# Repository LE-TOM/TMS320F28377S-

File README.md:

# TMS320F28377S-
使用176管脚的TMS320F28377S为主控引出来12路PWM和所有的模拟输入端口

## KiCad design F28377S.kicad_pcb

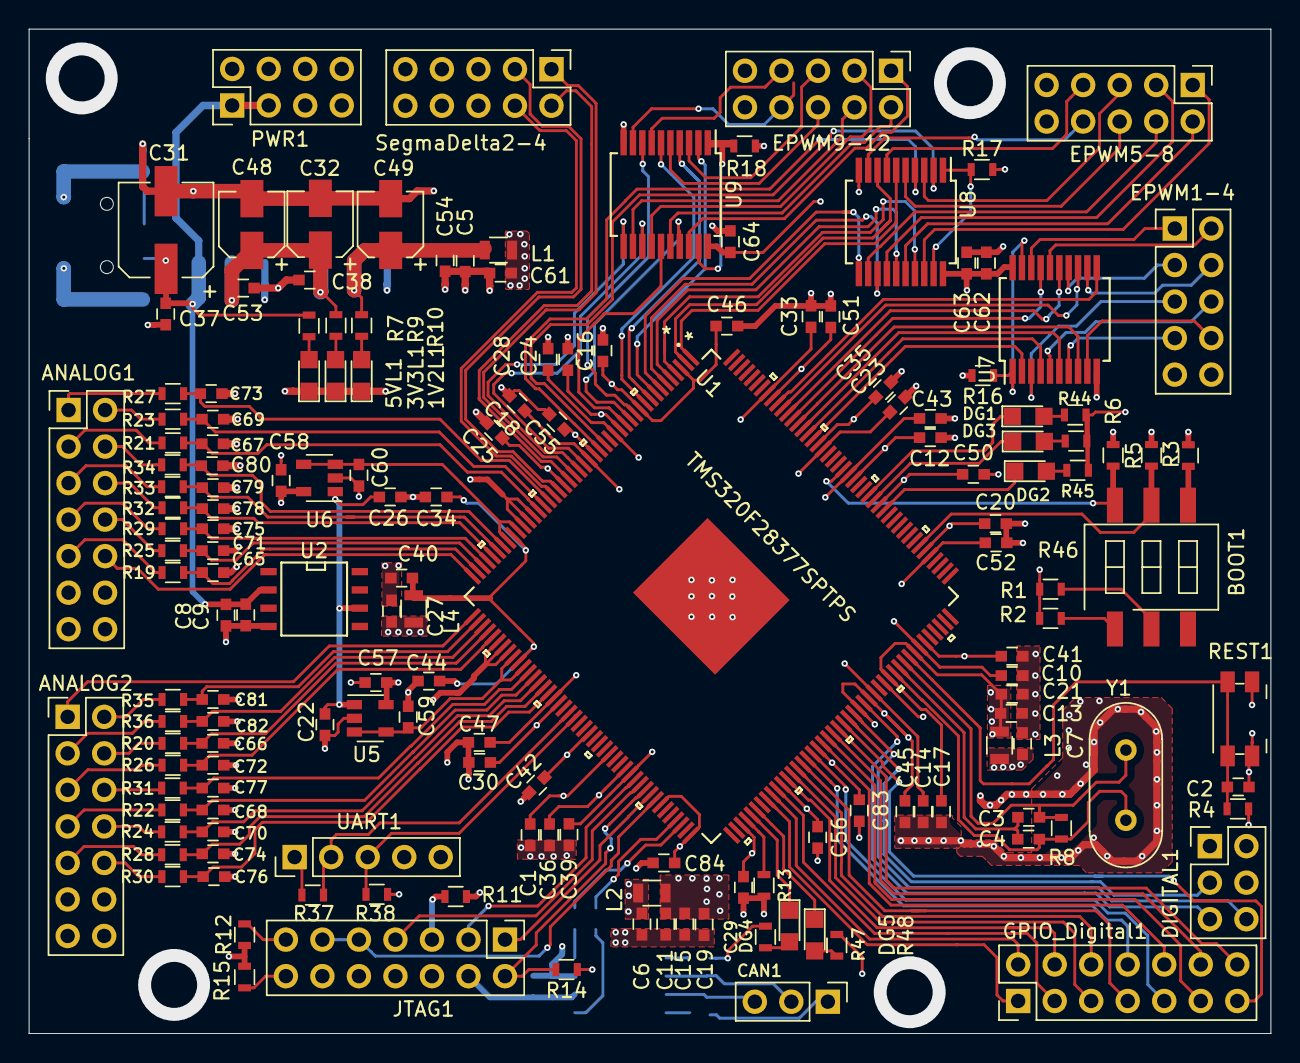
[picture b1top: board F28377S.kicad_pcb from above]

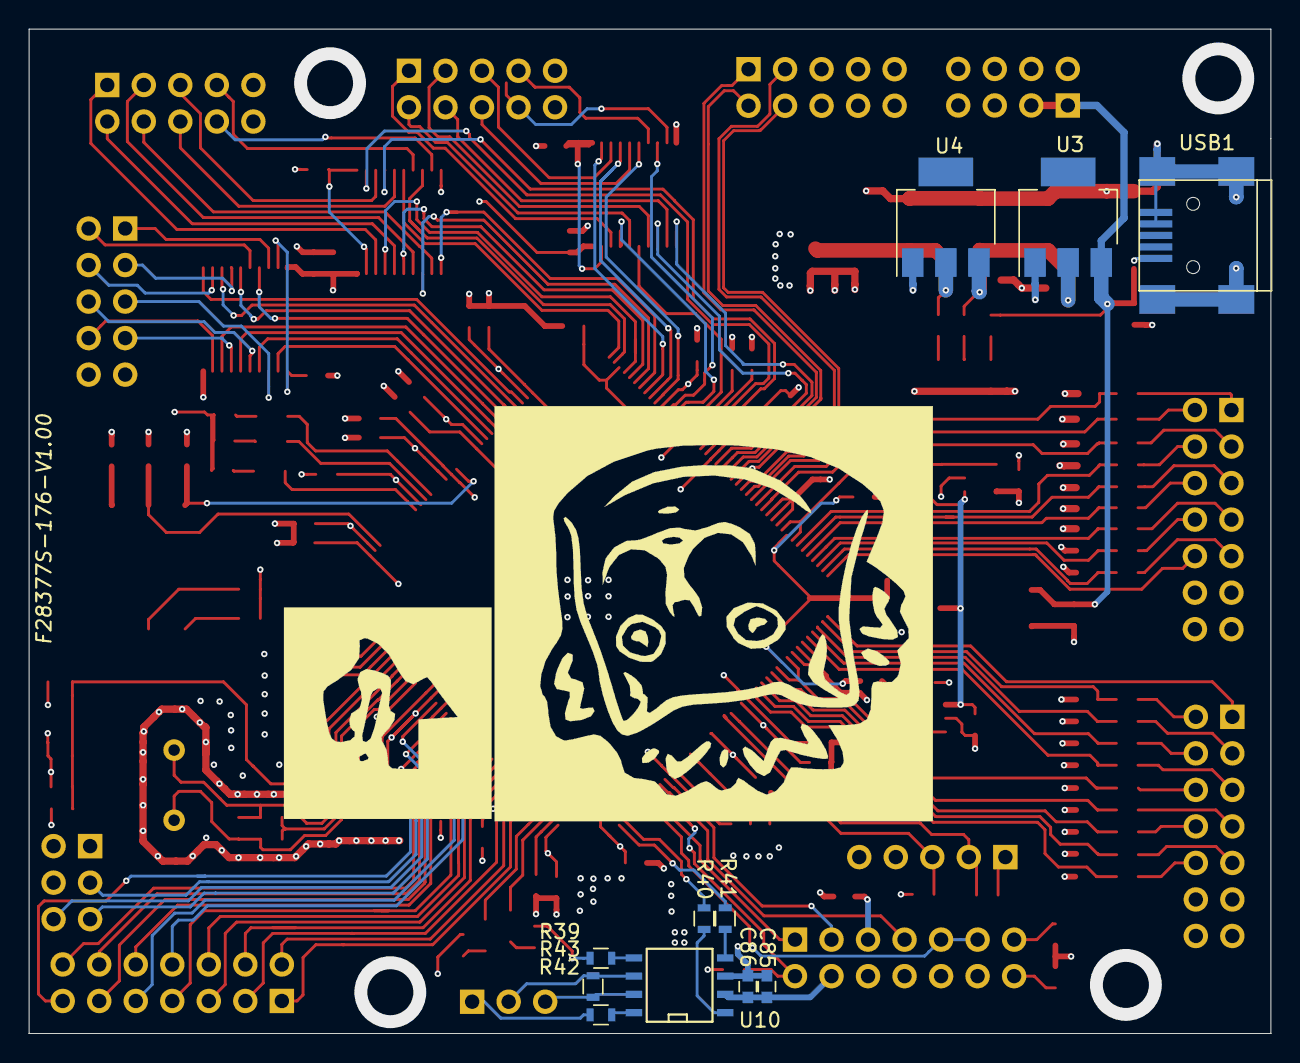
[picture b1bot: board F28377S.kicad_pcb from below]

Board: 4 copper layers, 86.4 x 69.8 mm, 172 parts (11 on the bottom side), 162 nets.

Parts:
1V2L1: BLED; LED_0805
3V3L1: GLED; LED_0805
5VL1: RLED; LED_0805
ANALOG1, ANALOG2: ANALOG; Pin_Header_Straight_2x07_Pitch2.54mm
BOOT1: BOOT; SW_DIP_x3_W8.61mm_Slide_LowProfile
C1, C2, C9, C11, C12, C15, C16, C17, C19, C20, C21, C24, C25, C26, C29, C30, C35, C36, C37, C38, C40, C41, C42, C44, C45, C46, C50, C51, C53, C54, C55, C56, C57, C58, C59, C60, C62, C63, C64, C83, C84, C86: 0.1u; C_0603
C3, C4: 25p; C_0603
C5, C6, C7, C10, C13, C14, C18, C23, C27, C28, C33, C34, C39, C43, C47, C52, C61: 2u2; C_0603
C8, C22, C85: 2.2u; C_0603
C31: 220u; CP_Elec_6.3x4.5
C32, C48, C49: 220u; CP_Elec_4x4.5
C65, C66, C67, C68, C69, C70, C71, C72, C73, C74, C75, C76, C77, C78, C79, C80, C81, C82: 100p; C_0603
CAN1: CAN; Pin_Header_Straight_1x03_Pitch2.54mm
DG1, DG2, DG3, DG4, DG5: DG1; LED_0805
DIGITAL1: DIGITAL; Pin_Header_Straight_2x03_Pitch2.54mm
EPWM1-4: EPWM1-4; Pin_Header_Straight_2x05_Pitch2.54mm
EPWM5-8: EPWM5-8; Pin_Header_Straight_2x05_Pitch2.54mm
EPWM9-12: EPWM9-12; Pin_Header_Straight_2x05_Pitch2.54mm
GPIO_Digital1: GPIO_Digital; Pin_Header_Straight_2x07_Pitch2.54mm
JTAG1: PROGRAME; Pin_Header_Straight_2x07_Pitch2.54mm
L1, L2, L3, L4: 200Ohm; R_0805
PWR1: PWR; Pin_Header_Straight_2x04_Pitch2.54mm
R1, R2: 820; R_0603
R3, R5, R6, R14: 2k2; R_0603
R4, R12, R15, R16, R17, R18, R37, R38, R39, R42: 4k7; R_0603
R7, R9, R44, R45, R46, R47, R48: 1k; R_0603
R8: 1M; R_0603
R10: 300; R_0603
R11, R19, R20, R21, R22, R23, R24, R25, R26, R27, R28, R29, R30, R31, R32, R33, R34, R35, R36, R40, R41: 100; R_0603
R13: 10k; R_0603
R43: 120; R_0603
REST1: SW_Push; Panasonic_EVQPUK_EVQPUB
SegmaDelta2-4: SegmaDelta2-4; Pin_Header_Straight_2x05_Pitch2.54mm
U1: TMS320F28377SPTPS
U2: REF196; SOIC-8-N
U3: AZ1117-3.3; SOT-223
U4: AZ1117-1.2; SOT-223
U5, U6: LM321; SOT-23-5
U7, U8, U9: 74HC244; SSOP-20_5.3x7.2mm_Pitch0.65mm
U10: SN65HVD230; SOIC-8-N
UART1: UART; Pin_Header_Straight_1x05_Pitch2.54mm
USB1: USB_B_Mini; USB_Mini-B
Y1: 10Mhz; Crystal_HC49-4H_Vertical

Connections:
+1V2: C5.1, C49.1, C54.1, L1.1, R10.1, U4.2
+3V3: ANALOG1.11, ANALOG1.12, ANALOG2.11, ANALOG2.12, C1.1, C6.1, C7.1, C27.1, C32.1, C38.1, C48.1, C53.1, C57.2, C58.2, C62.2, C63.2, C64.2, C85.2, C86.2, EPWM1-4.10, EPWM5-8.10, EPWM9-12.10, L2.1, L3.1, L4.1, PWR1.6, PWR1.8, R1.1, R2.1, R4.1, R9.1, R11.1, R12.1, R15.1, R37.1, R38.1, R39.1, R44.1, R45.1, R46.1, R47.1, R48.1, SegmaDelta2-4.6, SegmaDelta2-4.8, SegmaDelta2-4.10, U1.72, U1.119, U3.2, U4.3, U5.5, U6.5, U7.20, U8.20, U9.20, U10.3, UART1.1
+5V: C8.1, C9.1, C31.1, C37.1, PWR1.1, PWR1.3, R7.1, U2.2, U3.3, USB1.1
/ADCIN14: ANALOG1.10, U1.44
/ADCIN15: ANALOG2.1, U1.45
/ADCINA0: C65.1, R19.2, U1.43
/ADCINA1: C71.1, R25.2, U1.42
/ADCINA2: C75.1, R29.2, U1.41
/ADCINA3: C78.1, R32.2, U1.40
/ADCINA4: C79.1, R33.2, U1.39
/ADCINA5: C80.1, R34.2, U1.38
/ADCINB0: C81.1, R35.2, U1.46
/ADCINB1: C82.1, R36.2, U1.47
/ADCINB2: C66.1, R20.2, U1.48
/ADCINB3: C72.1, R26.2, U1.49
/ADCINC2: C67.1, R21.2, U1.31
/ADCINC3: C69.1, R23.2, U1.30
/ADCINC4: C73.1, R27.2, U1.29
/ADCIND0: C77.1, R31.2, U1.56
/ADCIND1: C68.1, R22.2, U1.57
/ADCIND2: C70.1, R24.2, U1.58
/ADCIND3: C74.1, R28.2, U1.59
/ADCIND4: C76.1, R30.2, U1.60
/BGPIO0: EPWM1-4.1, U7.18
/BGPIO1: EPWM1-4.2, U7.16
/BGPIO2: EPWM1-4.3, U7.14
/BGPIO3: EPWM1-4.4, U7.12
/BGPIO4: EPWM1-4.5, U7.3
/BGPIO5: EPWM1-4.6, U7.5
/BGPIO6: EPWM1-4.7, U7.7
/BGPIO7: EPWM1-4.8, U7.9
/BGPIO8: EPWM5-8.1, U8.18
/BGPIO9: EPWM5-8.2, U8.16
/BGPIO10: EPWM5-8.3, U8.14
/BGPIO11: EPWM5-8.4, U8.12
/BGPIO12: EPWM5-8.5, U8.3
/BGPIO13: EPWM5-8.6, U8.5
/BGPIO14: EPWM5-8.7, U8.7
/BGPIO15: EPWM5-8.8, U8.9
/BGPIO16: EPWM9-12.1, U9.18
/BGPIO17: EPWM9-12.2, U9.16
/BGPIO18: EPWM9-12.3, U9.14
/BGPIO19: EPWM9-12.4, U9.12
/BGPIO20: EPWM9-12.5, U9.3
/BGPIO21: EPWM9-12.6, U9.5
/BGPIO22: EPWM9-12.7, U9.7
/BGPIO23: EPWM9-12.8, U9.9
/EA0: ANALOG1.9, R19.1
/EA1: ANALOG1.8, R25.1
/EA2: ANALOG1.7, R29.1
/EA3: ANALOG1.6, R32.1
/EA4: ANALOG1.5, R33.1
/EA5: ANALOG1.4, R34.1
/EB0: ANALOG2.2, R35.1
/EB1: ANALOG2.3, R36.1
/EB2: ANALOG2.4, R20.1
/EB3: ANALOG2.5, R26.1
/EC2: ANALOG1.3, R21.1
/EC3: ANALOG1.2, R23.1
/EC4: ANALOG1.1, R27.1
/ED0: ANALOG2.6, R31.1
/ED1: ANALOG2.7, R22.1
/ED2: ANALOG2.8, R24.1
/ED3: ANALOG2.9, R28.1
/ED4: ANALOG2.10, R30.1
/GPIO0: U1.160, U7.2
/GPIO1: U1.161, U7.4
/GPIO2: U1.162, U7.6
/GPIO3: U1.163, U7.8
/GPIO4: U1.164, U7.17
/GPIO5: U1.165, U7.15
/GPIO6: U1.166, U7.13
/GPIO7: U1.167, U7.11
/GPIO8: U1.18, U8.2
/GPIO9: U1.19, U8.4
/GPIO10: U1.1, U8.6
/GPIO11: U1.2, U8.8
/GPIO12: U1.4, U8.17
/GPIO13: U1.5, U8.15
/GPIO14: U1.6, U8.13
/GPIO15: U1.7, U8.11
/GPIO16: U1.8, U9.2
/GPIO17: U1.9, U9.4
/GPIO18: U1.10, U9.6
/GPIO19: U1.12, U9.8
/GPIO20: U1.13, U9.17
/GPIO21: U1.14, U9.15
/GPIO22: U1.22, U9.13
/GPIO23: U1.23, U9.11
/GPIO24: SegmaDelta2-4.1, U1.24
/GPIO25: SegmaDelta2-4.2, U1.25
/GPIO26: SegmaDelta2-4.3, U1.27
/GPIO27: SegmaDelta2-4.4, U1.28
/GPIO28: R37.2, U1.64, UART1.2
/GPIO29: R38.2, U1.65, UART1.3
/GPIO38: R40.1, U1.85
/GPIO39: R41.1, U1.86
/GPIO44: DIGITAL1.6, U1.113
/GPIO45: DIGITAL1.5, U1.115
/GPIO49_DG4: DG4.1, U1.93
/GPIO50_DG5: DG5.1, U1.94
/GPIO52: GPIO_Digital1.1, U1.96
/GPIO53: GPIO_Digital1.2, U1.97
/GPIO54: GPIO_Digital1.3, U1.98
/GPIO55: GPIO_Digital1.4, U1.100
/GPIO56: GPIO_Digital1.5, U1.101
/GPIO57: GPIO_Digital1.6, U1.102
/GPIO58: GPIO_Digital1.7, U1.103
/GPIO59: GPIO_Digital1.8, U1.104
/GPIO60: GPIO_Digital1.9, U1.105
/GPIO61: GPIO_Digital1.10, U1.107
/GPIO62: GPIO_Digital1.11, U1.108
/GPIO63: GPIO_Digital1.12, U1.109
/GPIO64: GPIO_Digital1.14, U1.110
/GPIO65: GPIO_Digital1.13, U1.111
/GPIO66: DIGITAL1.3, U1.112
/GPIO72: BOOT1.5, R5.1, U1.139
/GPIO79_DG2: DG2.1, U1.146
/GPIO80_DG3: DG3.1, U1.148
/GPIO81_DG1: DG1.1, U1.149
/GPIO84: BOOT1.6, R6.1, U1.154
/RESET: C2.1, R4.2, REST1.2, U1.124
/TCK: JTAG1.9, JTAG1.11, U1.81
/TDI: JTAG1.3, U1.77
/TDO: JTAG1.7, U1.78
/TMS: JTAG1.1, U1.80
/TRST: BOOT1.4, R3.1
/TRST_N: JTAG1.2, R14.2, U1.79
/VDD: C10.1, C14.1, C18.1, C23.1, C28.1, C33.1, C39.1, C43.1, C47.1, C52.1, C61.1, L1.2, U1.16, U1.21, U1.61, U1.76, U1.117, U1.126, U1.137, U1.153, U1.158, U1.169
/VDDA: C34.1, C40.1, C44.1, L4.2, U1.36, U1.54
/VDDIO: C11.1, C12.1, C15.1, C16.1, C19.1, C20.1, C24.1, C25.1, C29.1, C30.1, C35.1, C36.1, C41.1, C42.1, C45.1, C46.1, C50.1, C51.1, C55.1, C56.1, C83.1, C84.1, L2.2, U1.3, U1.11, U1.15, U1.20, U1.26, U1.62, U1.68, U1.75, U1.82, U1.88, U1.91, U1.99, U1.106, U1.114, U1.116, U1.127, U1.138, U1.147, U1.152, U1.159, U1.168
/VDDOSC: C13.1, C17.1, C21.1, L3.2, U1.120, U1.125
/VREFHIA: C60.2, U1.35, U1.37, U6.3, U6.4
/VREFHIB: C59.2, U1.53, U1.55, U5.3, U5.4
/VSSOSC: C3.2, C4.2, U1.122
GND: 1V2L1.1, 3V3L1.1, 5VL1.1, ANALOG1.13, ANALOG1.14, ANALOG2.13, ANALOG2.14, C1.2, C2.2, C5.2, C6.2, C7.2, C8.2, C9.2, C10.2, C11.2, C12.2, C13.2, C14.2, C15.2, C16.2, C17.2, C18.2, C19.2, C20.2, C21.2, C22.2, C23.2, C24.2, C25.2, C26.2, C27.2, C28.2, C29.2, C30.2, C31.2, C32.2, C33.2, C34.2, C35.2, C36.2, C37.2, C38.2, C39.2, C40.2, C41.2, C42.2, C43.2, C44.2, C45.2, C46.2, C47.2, C48.2, C49.2, C50.2, C51.2, C52.2, C53.2, C54.2, C55.2, C56.2, C57.1, C58.1, C59.1, C60.1, C61.2, C62.1, C63.1, C64.1, C65.2, C66.2, C67.2, C68.2, C69.2, C70.2, C71.2, C72.2, C73.2, C74.2, C75.2, C76.2, C77.2, C78.2, C79.2, C80.2, C81.2, C82.2, C83.2, C84.2, C85.1, C86.1, CAN1.1, DIGITAL1.1, DIGITAL1.2, DIGITAL1.4, EPWM1-4.9, EPWM5-8.9, EPWM9-12.9, JTAG1.4, JTAG1.8, JTAG1.10, JTAG1.12, PWR1.2, PWR1.4, PWR1.5, PWR1.7, R3.2, R5.2, R6.2, R13.2, R14.1, R16.2, R17.2, R18.2, R42.2, REST1.1, SegmaDelta2-4.5, SegmaDelta2-4.7, SegmaDelta2-4.9, U1.32, U1.33, U1.34, U1.50, U1.51, U1.52, U1.177, U2.4, U3.1, U4.1, U5.2, U6.2, U7.10, U8.10, U9.10, U10.2, UART1.4, USB1.4, USB1.5, USB1.6
unnamed: 1V2L1.2, R10.2
unnamed: 3V3L1.2, R9.2
unnamed: 5VL1.2, R7.2
unnamed: BOOT1.1, R2.2
unnamed: BOOT1.2, R1.2
unnamed: C3.1, R8.1, U1.123, Y1.1
unnamed: C4.1, R8.2, U1.121, Y1.2
unnamed: C22.1, C26.1, U2.6, U5.1, U6.1
unnamed: CAN1.2, R43.1, U10.6
unnamed: CAN1.3, R43.2, U10.7
unnamed: DG1.2, R44.2
unnamed: DG2.2, R45.2
unnamed: DG3.2, R46.2
unnamed: DG4.2, R47.2
unnamed: DG5.2, R48.2
unnamed: JTAG1.5, R11.2
unnamed: JTAG1.13, R12.2
unnamed: JTAG1.14, R15.2
unnamed: R13.1, U1.92
unnamed: R16.1, U7.1, U7.19
unnamed: R17.1, U8.1, U8.19
unnamed: R18.1, U9.1, U9.19
unnamed: R39.2, U10.5
unnamed: R40.2, U10.1
unnamed: R41.2, U10.4
unnamed: R42.1, U10.8

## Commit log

2020-08-23 upload
    上传硬件原理图以及PCB

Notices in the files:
parts and their libraries:
Copyright 2016 Accelerated Designs. All rights reserved.
